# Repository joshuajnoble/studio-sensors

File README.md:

===============================================
frog studio sensor
===============================================

Let's keep it simple at first: there's a server and you can pull info from it. Here's what some of that info looks like:

```
[{"id":134,"sensor_id":1,"time":"2014-03-24T23:48:55.442Z","light":1,"sound":114,"movement":1,"temp":18,"humidity":147,"brightness":0},
{"id":135,"sensor_id":1,"time":"2014-03-24T23:49:20.120Z","light":1347,"sound":562,"movement":0,"temp":34,"humidity":3,"brightness":0}]
```

Whoa. That's JSON!

The frog studio sensors log all their data up there to my server every 15 seconds. 

Ok, so we have a few things in there:

* sensor_id: what sensor is it?
* studio: what studio is it in?
* zone: what part of the studio is it in?
* time: that's a timestamp (this is in GMT)
* sound: scale from 0-30 (afaict)
* movement: has anything moved in that zone in the last 30 seconds?
* humidity: what's the relative humidity (percent)
* temperature: Celsius
* light: light frequency in values from 480-600 (afaict)
* brightness: not being used right now

The raspberry pi just logs its data using a URL like:

`http://OUR_URL:3000/?i=1&l=343&s=232&t=22&h=33&m=0&&studio=sea&zone=1`

You can make fake (test) posts all you want.

===============================================
VISUALIZATION
===============================================

Where's the visualization? Good question. Have you made one yet? No? Well there's your answer. This is meant to look different to each studio. There are a few basic pattern goes like so:

`/view?params`

Let's look at some more stuff in here. You're *probably* going to want to just use the following:

`URL:3000/view?studio=SEA&begindate=24032014&begintime=1600&enddate=24032014&endtime=1700`

That gives you all the data from Seattle from 24032014:1600 to 24032014:1700 thats DDMMYY:24HR

There is more though, be warned though, these datasets can get massive and pulling them all is *slow*

All studios by date:

`URL:3000/view?begindate=24032014&begintime=1600&enddate=24032014&endtime=1700`

The last reading by zone

`URL:3000/view?studio=SEA&zone=1&last=1`

All readings by zone

`URL:3000/view?studio=SEA&zone=1`

All readings by sensorid (good for debugging)

`URL:3000/view?id=1`

Timeboxed view of a particular zone:

`URL:3000/?i=1&l=343&s=232&t=22&h=33&m=0&&studio=sea&zone=1`

All readings from the last hour

`URL:3000/view?recent=1&zone=1&studio=SEA`

The last reading of a studio

`URL:3000/view?now=1&studio=SEA`

Want more? It's very easy to add. Just take a look at studio-sensors/server.js for tips on how to make it better.

===============================================
DEVICE INFO
===============================================

The device is a Raspberry pi with some sensors on it. The first thing the device does is start up, report its IP, studio (within frog), location (zone), and then get a sensor id that will follow it as long as it (it, in this case being the SD card) exists.

This is accessed like so:

`$URL/get_id?studio=SEA&zone=1&ip=172.189.128.112`

When the machine is kicked off the network and hops back on that it updates its IP. This is done like so:

`$URL/update_id?id=1&ip=172.189.128.112`

The id you see there is the same ID that is retrieved when the machine is first started up. 

Why is this "id => IP" mapping important? Well, so that you can always SSH into your device and see what's up with it, if it crashed, if the DHT22 burnt out, etc. That's what makes it worthwhile to have everything on the RPI.

To configure the device to run the studio sensor program you need to do a few different things first.

1) Install the drivers for the Edimax EW-7811Un USB WiFi chip

http://www.andreagrandi.it/2014/09/02/how-to-configure-edimax-ew-7811un-wifi-dongle-on-raspbian/

2) Install pigpio

http://abyz.co.uk/rpi/pigpio/

3) Install git

sudo apt-get install git

4) Install Adafruit DHT22 driver

https://github.com/adafruit/Adafruit_Python_DHT

===============================================
SERVER INFO
===============================================

I have my server set up to use upstart to start up our node application, it's logging to :"/etc/init/studioapi.conf" at the moment so you can see what's going on with it.

I'm using ec2 ubuntu.

To get things set up I just did the following:

`sudo apt-get install postgres node`

then 

`sudo vim /etc/postgresql/9.3/main/postgresql.conf`

uncomment the line that says: `#listen_addresses = 'localhost' `
then
`sudo vim /etc/postgresql/9.3/main/pg_hba.conf`

then

`sudo service postgresql start`

then

```
sudo -i -u postgres
ubuntu@ip-172-31-30-171:~$ sudo -i -u postgres
postgres@ip-172-31-30-171:~$ psql
psql (9.3.5)
Type "help" for help.

ALTER USER postgres WITH PASSWORD '$password';
```

Create a job:

`sudo vim /etc/init/studioapi.conf`

then add:

```
description "node.js server"
author     "josh"

# used to be: start on startup
# until we found some mounts weren't ready yet while booting:
start on started mountall
stop on shutdown

# Automatically Respawn:
respawn
respawn limit 99 5

script
    # Not sure why $HOME is needed, but we found that it is:
    export HOME="/root"

    exec /usr/bin/node /home/joshuajnoble/studio-sensors/server.js >> /var/log/node.log 2>&1
end script

post-start script
   # Optionally put a script here that will notifiy you node has (re)started
   # /root/bin/hoptoad.sh "node.js has started!"
end script
```

===============================================
DB INFO
===============================================

Creating the DB is pretty simple:
```
create database sensordata;

create table sensors ( studio varchar(3), zone varchar(10), id integer, constraint uid unique(id), ip varchar(16) );

ALTER TABLE sensors ADD COLUMN key varchar(30);

ALTER TABLE sensors ADD CONSTRAINT uniquekey UNIQUE (key);

create table readings ( id serial, sensor id int not null, time timestamp with time zone not null, light int not null, sound int not null, movement int not null, temp int not null, humidity int not null, brightness int not null, zone varchar(30) not null, studio varchar(30) not null);
```

===============================================
Troubleshooting
===============================================

Can't get the Pi online?

Try making a little entry in crontab to make the RaspberryPi ping your router every minute. This will ensure that your wifi connection will stay alive. To edit crontab just type (from pi user, you don’t need to be root):

`crontab -e`

and insert this line at the end:

`*/1 * * * * ping -c 1 192.168.0.1`

where 192.168.0.1 is the IP of your router. I don't know what your studios router address will be, so you'll have to figure that out.

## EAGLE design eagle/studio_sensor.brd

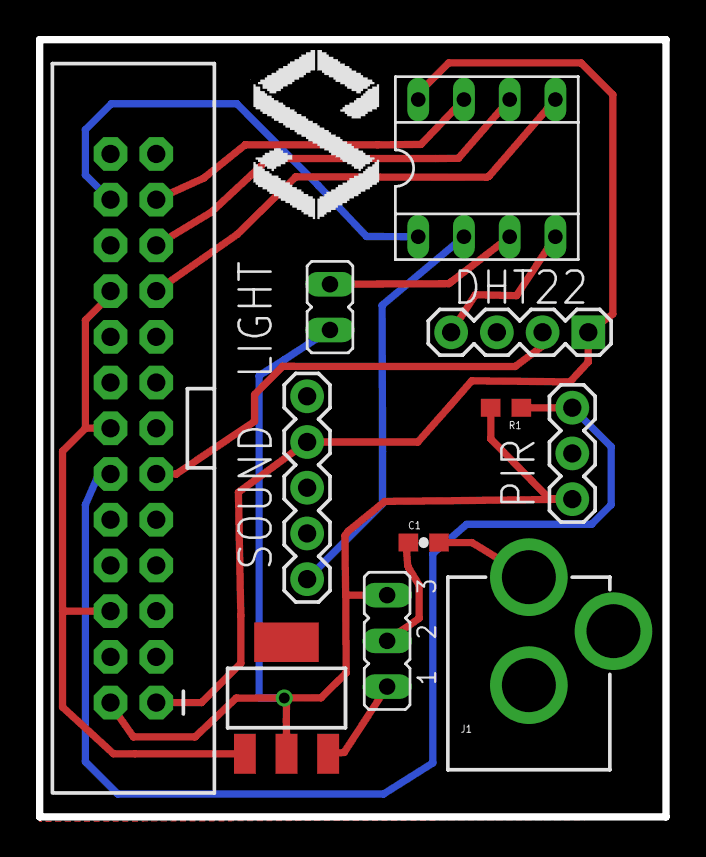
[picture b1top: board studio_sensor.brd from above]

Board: 2 copper layers, 34.8 x 43.2 mm, 11 parts (0 on the bottom side), 14 nets.

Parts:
C1: 0603-CAP
IC1: SOT223
IC3: SOCKET-08
J1: POWER_JACKPTH; POWER_JACK_PTH
JP1: RASPBERRYPI-GPIOPTH; 2X13-SHROUDED
JP2: 1X04
JP3: JP1
JP4: 1X03
JP5: 1X05
JP6: JP2
R1: 0603

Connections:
GND: IC1.1, IC3.4, J1.GND, JP1.6, JP1.9, JP1.14, JP1.20, JP1.25, JP2.4, JP4.2, JP5.1
unnamed: IC1.2, JP1.2, JP3.1, JP4.1, JP6.3, R1.2
unnamed: IC3.8, JP1.1, JP2.1, JP5.2
unnamed: IC3.3, JP3.2
unnamed: IC3.7, JP1.23
unnamed: IC3.6, JP1.21
unnamed: IC3.5, JP1.19
unnamed: IC3.1, JP1.24
unnamed: IC3.2, JP5.5
unnamed: IC1.3, JP6.1
unnamed: JP1.11, JP2.2
unnamed: C1.2, J1.PWR
unnamed: C1.1, JP6.2
unnamed: JP1.12, JP4.3, R1.1

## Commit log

2014-03-12 Initial commit.
2014-03-15 adding arduino files
2014-03-18 adding proper URL, adjusting interrupt
2014-03-19 Adding Dockerfile and README for setting up postgresql database.
2014-03-19 Updating readme with accurate instructions for connecting to postgresql db.
2014-03-19 Adding some more information for connecting to the postgresql db.
2014-03-20 add a server
2014-03-25 updating server and arduino
2014-03-25 updating readme
2014-03-26 cleaning up arduino app
2014-04-14 updating to read PIR correctly
2014-04-17 re-adding studio sensors
2014-05-01 updating server, last ditch try w/the watchdog timer
2014-06-09 adding rpi
2014-06-10 cleanup, moving to c++ instead of just C
2014-06-11 these got removed?
2014-06-11 adding README
2014-06-12 adding tests
2014-06-13 dht22 updates
2014-06-13 updating dht sensor reading
2014-06-16 plenty more cleanup
2014-06-16 adding a makefil
2014-06-16 updating timing and adding PIR
2014-06-19 adding wifly test
2014-06-19 moving to string
2014-06-19 updating loop to account for network loss
2014-06-23 adding adafruit pi_mmio lib instead
2014-06-23 typo in spi_ioc_transfer
2014-06-23 having some C/C++ compile problems
2014-06-25 closer on pi_mmio
2014-06-25 adding test for mmio
2014-06-25 debugging
2014-07-09 adding a startup script
2014-07-11 adding an spi_test
2014-07-11 cleaning up dht test, works
2014-07-21 going to need to roll everything back to BCM :/
2014-07-22 updating tsl235
2014-07-22 adding output
2014-07-23 adding studio sensors py
2014-07-29 adding README for py setup
2014-07-31 some small change
2014-08-08 getting back changes lost in vim weirdness
2014-08-08 adding startup script
2014-08-08 undo overwrite'
2014-08-08 error check
2014-08-08 updating pins to match eagle
2014-08-08 adding schematics
2014-08-20 cleaning up start
2014-08-20 no more tsl235
2014-09-12 updating studio sensors
2014-09-19 Added a start script in prep for AWS deployment
2014-09-30 Update db instructions
2014-10-04 updating to ifup/down wlan on errs
2014-10-14 bad pcall typo
2014-10-14 many updates
2014-10-14 updates for correct pins
2014-10-15 adding sound averaging
2014-10-16 sensor readings every 10min
2014-10-16 no more hex in values
2014-10-17 adding log record
2014-10-20 no more leaking FDs
2014-10-20 adding zone+last
2014-10-20 bug zone+last
2014-10-20 redoing DB
2014-10-20 fixing on the fly
2014-10-20 updating sensor
2014-10-21 was fixing
2014-10-21 updating py for new JS api
2014-10-21 update build script
2014-10-21 server insert fixes
2014-10-21 updating studio sensor
2014-10-28 changing DB name
2014-10-28 updating IP + PORT
2014-10-28 updateing server
2014-11-04 updating script
2014-11-04 adding psql
2014-11-04 sensor key must be unique
2014-11-04 creating update function
2014-11-06 server updates
2014-11-07 adding more error handling for bad networks
2014-11-07 string zone
2014-11-07 tagging
2014-11-07 massive cleanup
2014-11-07 more cleanup
2014-11-10 adding hwaddr
2014-11-11 adding mac=>studio,zone
2014-11-11 error
2014-11-11 cleaningup studio sensors
2014-11-12 adding time stamps to error messages
2014-11-12 making a GH pages
2014-11-12 adding a bunch of images
2014-11-12 better website
2014-11-12 adding err for no MAC address set
2014-11-13 adding MAC config
2014-11-13 imags
2014-11-13 updating instructions
2014-11-13 adding get_ip
2014-11-13 more tutorial
2014-11-17 making names uniform
2014-11-17 making no mac return 409
2014-11-17 error handling for no MAC
2014-11-21 case mismatch on MAC
2014-11-21 update docs
2014-11-21 favicon

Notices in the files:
parts and their libraries:
SparkFun-Boards: Licensing: Creative Commons ShareAlike 4.0 International - https://creativecommons.org/licenses/by-sa/4.0
